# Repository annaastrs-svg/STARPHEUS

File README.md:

STARPHEUS BOT
----

https://annaastrs-svg.github.io/STARPHEUS-PAG/
Take a look to the web page !

[also my build journal :P](JOURNAL.md)

Orpheus Bot It's a robot inspired by the Hack Club mascot (Orpheus).
Starpheus is a Wall-E type robot.
You can control it with a LogiTECH controller (you control its neck with an MG996R servo motor and the TT motors). 
It has 3 OLEDs that make up its eyes and mouth, simulates emotions with basic state machines (scared, happy, sleepy, neutral),
and uses an HC ultrasonic sensor to avoid collisions.
NOTE: this is a rlly full demo jsjjs 

Design
-------
The complete BOT is 31 cm tall, and 31 cm long counting the arms, its designed to look cool (idk if it is,for me it is), i wanted it to be like a Walle-E type.

The design was made so that our little Starpheus isn't heavy and has good mobility.

It has details to be able to put our components and hollow parts so that the chassis isn't heavy and has more mobility, as I already mentioned.

details:

holes for 3 OLED screens (2x 0.96 & 0.91 )
a reset button at the back
the ESP32-S3 connector at the back
the ultrasonic sensor in the front
and spots to attach the motors.

I'm an amateur, this is my biggest solo project so far, and I like to challenge myself.
Honestly, I struggled a lot with this project. I changed everything from one moment to the next thousands of times. It was going to have computer vision and an infrared sensor so you could pet it, it was going to be semi-autonomous, but it was very ambitious. This is the beginning of Starpheus; in the future, I’ll improve it and all these ideas will be more than just ideas. 

PCB
---

CAD
---

I made this EXCEL with all the connections :B

Videos
---
sorry about the quality and my room mess...

https://github.com/user-attachments/assets/39a8d48d-7ff0-484d-94e4-6cae62331124

https://github.com/user-attachments/assets/a8ff2db2-2984-4ae0-9904-147b8f435752

BOM 
--
| Component         | Description                                | Unit | Cost    | Distibutor    | Link                                                                                                                                                                        |
|-------------------|--------------------------------------------|------|---------|---------------|-----------------------------------------------------------------------------------------------------------------------------------------------------------------------------|
| ESP32-S3          | Micro Controler, send code to components   | 1    | $34.91  | AlliExpress        | https://es.aliexpress.com/item/1005009212121307.html?src=bing&exp_tag=pcgcp&albch=shopping&acnt=135095331&albcp=555291703&albag=1299623925852708&slnk=&trgt=pla-2333026235563924&plac=&crea=81226553419370&netw=o&device=c&mtctp=e&utm_source=Bing&utm_medium=shopping&utm_campaign=PA_Bing_MX_Pmax_3C_MAXvalue_20250206_newstore&utm_content=3C&utm_term=ESP32-S3&msclkid=053bb998d0691e21b9cbd3a79d374743&aff_fcid=c5ba799bdfd04e76ae5a24437fb695cd-1782533500453-03069-UneMJZVf&aff_fsk=UneMJZVf&aff_platform=aaf&sk=UneMJZVf&aff_trace_key=c5ba799bdfd04e76ae5a24437fb695cd-1782533500453-03069-UneMJZVf&terminal_id=5927158648684954809663ec4040b6d2&afSmartRedirect=n&gatewayAdapt=glo2esp  |
| DRV8833           | H bridge for motors and control PWM        | 1    | $2.50 | AlliExpress   | https://es.aliexpress.com/item/1005006151344347.html?src=bing&exp_tag=pcgcp&albch=shopping&acnt=135095331&albcp=555291703&albag=1299623925852708&slnk=&trgt=pla-2333026235563924&plac=&crea=81226553419370&netw=o&device=c&mtctp=e&utm_source=Bing&utm_medium=shopping&utm_campaign=PA_Bing_MX_Pmax_3C_MAXvalue_20250206_newstore&utm_content=3C&utm_term=drv8833+bateria+pinout&msclkid=bc6fd8323a4012783781b20d77d54aed&aff_fcid=9159e0ecdd304c6abaf17352f823a6c3-1782533528389-07870-UneMJZVf&aff_fsk=UneMJZVf&aff_platform=aaf&sk=UneMJZVf&aff_trace_key=9159e0ecdd304c6abaf17352f823a6c3-1782533528389-07870-UneMJZVf&terminal_id=5927158648684954809663ec4040b6d2&afSmartRedirect=n&gatewayAdapt=glo2esp |
| OLED.96           | Display, shows data (orpheus eyes)         | 2    | $4.49   | Mercado Libre | https://articulo.mercadolibre.com.mx/MLM-705156753-display-pantalla-oled-128x64-096-para-arduino-_JM?searchVariation=63044404311                                            |
| OLED.91           | Display, shows data (orpheus mouth)        | 1    | $1.31   |   MercadoLibre   |https://www.mercadolibre.com.mx/pantalla-oled-azul-128x32-i2c-091/p/MLM2068167145?pdp_filters=item_id%3AMLM1478945642&from=gshop&matt_tool=15920969&matt_word=&matt_source=microsoft&matt_campaign_id=571305430&matt_ad_group_id=1177579225794197&matt_match_type=e&matt_network=o&matt_device=c&matt_creative=&matt_keyword=&matt_ad_position=&matt_ad_type=&matt_merchant_id=50038545&matt_product_id=MLM2068167145-product&matt_product_partition_id=4577198197450241&matt_target_id=pla-4577198197450241&msclkid=9ee6e6b3969d135712098c8cd8b2aa43&utm_source=bing&utm_medium=cpc&utm_campaign=MLM_ML_BING_AO_CE-ALL-ALL_X_PLA_ALLB_TXS_ALL&utm_term=4577198197450241&utm_content=CE  |
| HC-SR04           | Ultra sonic sensor, meausres distance      | 1    | $2.96   | Mercado Libre |https://www.mercadolibre.com.mx/sensor-de-distancia-hc-sr04-ultrasonico/p/MLM2039690988?pdp_filters=item_id%3AMLM571261161&from=gshop&matt_tool=15920969&matt_word=&matt_source=microsoft&matt_campaign_id=571305430&matt_ad_group_id=1177579225794197&matt_match_type=e&matt_network=o&matt_device=c&matt_creative=&matt_keyword=&matt_ad_position=&matt_ad_type=&matt_merchant_id=50038545&matt_product_id=MLM2039690988-product&matt_product_partition_id=4577198197450205&matt_target_id=pla-4577198197450205&msclkid=7707b5d9707f1734f956dfe63e3cd614&utm_source=bing&utm_medium=cpc&utm_campaign=MLM_ML_BING_AO_CE-ALL-ALL_X_PLA_ALLB_TXS_ALL&utm_term=4577198197450205&utm_content=CE              |
| MG-996R           | Servo Motor, orpheus neck                  | 1    | $7.33   | Amazon | https://www.amazon.com.mx/MG996R-55G-servomotor-Helic%C3%B3ptero-Arduino/dp/B0D7M2Y2BR/ref=asc_df_B0D7M2Y2BR?tag=mxbngshpdsk-20&linkCode=df0&hvadid=82395061852819&hvnetw=o&hvqmt=e&hvbmt=be&hvdev=c&hvlocint=&hvlocphy=151131&hvtargid=pla-4585994287787208&psc=1&msclkid=e6a7df47010d115d6c8eb5784f56fd7d                |
| tt engines        | Movement or orpheus bot                    | 2    | $4.00   | AlliExpress   | https://es.aliexpress.com/item/1005010779121177.html?src=bing&exp_tag=pcgcp&albch=shopping&acnt=135095331&albcp=555291703&albag=1299623925852708&slnk=&trgt=pla2333026235563924&plac=&crea=81226553419370&netw=o&device=c&mtctp=e&utm_source=Bing&utm_medium=shopping&utm_campaign=PA_Bing_MX_Pmax_3C_MAXvalue_20250206_newstore&utm_content=3C&utm_term=motores+tt&msclkid=4604d372fbfe14c3e344b94db561072e&aff_fcid=906d11c52e1f4a55975907ebcbe682d9-1782533793058-08454-UneMJZVf&aff_fsk=UneMJZVf&aff_platform=aaf&sk=UneMJZVf&aff_trace_key=906d11c52e1f4a55975907ebcbe682d9178253379305808454UneMJZVf&terminal_id=5927158648684954809663ec4040b6d2&afSmartRedirect=n&gatewayAdapt=glo2esp                      |
| buck converters   | For Voltage Protecction of the components  | 3    | $6.76   | Amazon   |  https://www.amazon.com.mx/Converter-Aumento-Ajustable-Reguladora-Conector/dp/B09Q8YTQXB/ref=sr_1_8?adgrpid=1165484206288746&dib=eyJ2IjoiMSJ9.TruDAKrU15d416ylBh8ulJJTz2d1TfT8EN7e9dJkodyHHH1od58L1fPMujRYPdf-iyD65iDMp7quqMR4rHF_oqQ558FzdXad7U6iBqxnKLUVJht0rHOsNf8Z6rRik0cXkLeRpQ79jHSn8AZXH9v3RqYukknHhFHUJGS6Di-PsSoyVzjTEjihnYqx9SSuxegqpyq5nz4iXMXztNyK1VH4imimKkbHgfz2UMPh53j9DiQde3CUSugjy8Pt4Wz_rNj58OK0CVWZDV5O15XB4WieNaAyq5raAqeb0MVdrpo1Y.y5zIeOKKhuF_8CNMwzP23gZmRT9i20QQBFSd3UYRtRU&dib_tag=se&hvadid=72843055995125&hvbmt=be&hvdev=c&hvlocphy=151131&hvnetw=o&hvqmt=e&hvtargid=kwd72843484889146%3Aloc119&hydadcr=14088_13417505&keywords=buck+converter&mcid=dc583b2887ca38368f6f683dde6ef2f0&msclkid=d19ed79b5dba1030403cbda4130e4359&qid=1782533818&sr=8-8&ufe=app_do%3Aamzn1.fos.de93fa6a-174c-4df7-be7c-5bc8e9c5a71b                        |
| Resistors 1k      | Kit of resistores, It helps with voltages  | 3    | $1.67   | Amazon   |https://www.amazon.com.mx/Resistencias-Metal-Film-Resistencia-Electr%C3%B3nicos/dp/B0CT529YD5/ref=sr_1_1_sspa?adgrpid=1166582601138475&dib=eyJ2IjoiMSJ9.NBcDPJqTYOjth7gdSySQirqF57sxDL8VWFTI05vC9nj6McOg-YSBZe8EXRi0eC_2E7MKzibLxM7QeVHcHB-Ko1-ebCdCLmKiHIZk1JfymyTa8jkAW23FNCHLAMJkkHtmW02T_EOZNTaL9eMtZ01eDVyzcTlr31lhvyVbtM1L0ijvk4gIRgnyGEiU9Rh7HpPkpj4SuspiLWUM5Q-W2VtRxNUT5J1G7SqDUZ1eaECu0euRlOkuUC3OyOBl_NhPJ95YzFsbwiseZHjBIxn4nGSkh16EDyRwq-q83riR1-KiOHo.1nvw0EbnL_xicWZ96wra5RXpQehdrYCikaisVadVuLE&dib_tag=se&hvadid=72911645984567&hvbmt=be&hvdev=c&hvlocphy=151131&hvnetw=o&hvqmt=e&hvtargid=kwd-72911986116600%3Aloc-119&hydadcr=11033_13513854&keywords=resistor+1k+ohm&mcid=bc221745620433ce85d0638f9c2af89e&msclkid=87cf17f18a9a186803f37dcec453b658&qid=1782533835&sr=8-1-spons&ufe=app_do%3Aamzn1.fos.de93fa6a-174c-4df7-be7c-5bc8e9c5a71b&sp_csd=d2lkZ2V0TmFtZT1zcF9hdGY&psc=1                |
| Capacitores 470uf | Kit of Capacitores, It helps with voltages | 3    | $1.21   | AlliExpress   | https://es.aliexpress.com/item/1005006079381755.html?src=bing&exp_tag=pcgcp&aff_fcid=30b0bfb162a64103b8094d08710fba9a-1782533862684-02992-UneMJZVf&aff_fsk=UneMJZVf&aff_platform=aaf&sk=UneMJZVf&aff_trace_key=30b0bfb162a64103b8094d08710fba9a-1782533862684-02992-UneMJZVf&terminal_id=5927158648684954809663ec4040b6d2&afSmartRedirect=n&gatewayAdapt=glo2esp             |
| Potobard          | Helps With the wiring                      | 1    | $3.41   | Amazon   | https://www.amazon.com.mx/Protoboard-MB-102-Prototipo-soldadura-unidades/dp/B08BCLRLTQ/ref=asc_df_B08BCLRLTQ?tag=mxbngshpdsk-20&linkCode=df0&hvadid=82944817571862&hvnetw=o&hvqmt=e&hvbmt=be&hvdev=c&hvlocint=&hvlocphy=151131&hvtargid=pla-4586544042717891&psc=1&msclkid=0dd1b50556fd178a90addf3a180881ad             |
| Wires Dupont      | Kit, Conects the components                | 1    | $1.79   | Amazon   | https://www.amazon.com.mx/Cables-Pruebas-Opcionales-Surtido-Multicolor/dp/B0DKD315BQ/ref=asc_df_B0DKD315BQ?tag=mxbngshpdsk-20&linkCode=df0&hvadid=82738659152219&hvnetw=o&hvqmt=e&hvbmt=be&hvdev=c&hvlocint=&hvlocphy=151131&hvtargid=pla-4586337884680739&psc=1&msclkid=e88ac20d4e861fde514ea832018665df         |
| Push Botton       | I added for a RST button of ESP32 ()       | 1    | $3.35   | Ebay |     https://www.ebay.com/itm/376667835321?chn=ps&_trkparms=ispr%3D1&amdata=enc%3A1-WCPs7ILQcmM3srRcIAPjQ30&norover=1&mkevt=1&mkrid=711-170539-829218-7&mkcid=2&itemid=376667835321&targetid=4580290580883290&device=c&mktype=&googleloc=151131&poi=&campaignid=605836810&mkgroupid=1227056202074386&rlsatarget=pla-4580290580883290&abcId=&merchantid=51291&msclkid=44e01bfe6e771c83f5b171c1217a5493                                |

There are a lot of components, it's a bit tedious but worth it. I will implement an ESP32 Cam in the future and they cost 3 bucks because I have a spare one. I recommend buying lots of batteries!!

ASSEMBLY 
---

| Orpheus Connections |                 |              |              |           |   |           |                 |                 |             |              |                 |
|---------------------|-----------------|--------------|--------------|-----------|---|-----------|-----------------|-----------------|-------------|--------------|-----------------|
| Come From           |                 | Goes To      |              |           |   | Come From |                 | Goes To         |             | Goes To      |                 |
| Component           |             Pin | Component    | Pin          |           |   | Component |             Pin | Component       | Pin         | Component    |             Pin |
| ESP32 S3            | 9               | OLED 1       | SCK          |           |   | Buck 2    | out +           | Capacitor 470uf | Positive +  | MG996R       | 5V              |
| ESP32 S3            | 8               | OLED 1       | SDA          |           |   |           |                 | Capacitor 470uf | Negative -  | Protoboard 1 | Negative        |
| ESP32 S3            | 14              | MG996R       | S            |           |   | Buck 2    | out -           | Protoboard1     | Negative -  |              |                 |
| ESP32 S3            | 10              | OLED 2       | SDA          |           |   | Buck 2    | in +            | Protoboard 2    | Positive +  |              |                 |
| ESP32 S3            | 11              | OLED 2       | SCK          |           |   | Buck 2    | in -            | Protoboard1     | Negative -  |              |                 |
| ESP32 S3            | 38              | OLED 3       | SDA          |           |   |           |                 |                 |             |              |                 |
| ESP32 S3            | 39              | OLED 3       | SCK          |           |   | Buck 1    | out +           | Capacitor 470uf | Positive +  | DRV8833      | 5V              |
| ESP32 S3            | 15              | DRV8833      | IN1          | A         |   |           |                 | Capacitor 470uf | Negative -  | Protoboard 1 | Negative        |
| ESP32 S3            | 16              | DRV8833      | IN2          | A         |   | Buck 1    | out -           | Protoboard 1    | Negative    |              |                 |
| ESP32 S3            | 17              | DRV8833      | IN3          | B         |   | Buck 1    | in +            | Protoboard 2    | Positive +  |              |                 |
| ESP32 S3            | 18              | DRV8833      | IN4          | B         |   | Buck 1    | in-             | Protoboard 1    | Negative -  |              |                 |
| ESP32 S3            | 5               | HC-SR04      | TRIG         |           |   |           |                 |                 |             |              |                 |
| ESP32 S3            | 6               | R1 (1kohm)    | ECHO         | R2 (2kohm) |   | BATTERY   | OUT +           | Protoboard 2    | Positive +  |              |                 |
| MG996R              | GND             | Protoboard 1 | Negative -   |           |   | BATTERY   | OUT -           | Protoboard 1    | Negative -  |              |                 |
| OLED 0.96  (1 & 2)  | GND             | Protoboard 1 | Negative -   |           |   |           |                 |                 |             |              |                 |
| OLED 0.96  (1 & 2)  | 5V              | Protoboard 1 | Positive +   |           |   |           |                 |                 |             |              |                 |
| OLED 0.91           | GND             | Protoboard 1 | Negative -   |           |   |           |                 |                 |             |              |                 |
| OLED 0.91           | 5V              | Protoboard 1 | Positive +   |           |   |           |                 |                 |             |              |                 |
| HC-SR04             | GND             | Protoboard 1 | Negative -   |           |   |           |                 |                 |             |              |                 |
| DRV8833             | GND             | Protoboard 1 | Negative -   |           |   |           |                 |                 |             |              |                 |
| DRV8833             | OUT1            | MOTOR A      | NO POLARIDAD |           |   |           |                 |                 |             |              |                 |
| DRV8833             | OUT2            | MOTOR A      | NO POLARIDAD |           |   |           |                 |                 |             |              |                 |
| DRV8833             | OUT3            | MOTOR B      | NO POLARIDAD |           |   |           |                 |                 |             |              |                 |
| DRV8833             | OUT4            | MOTOR B      | NO POLARIDAD |           |   |           |                 |                 |             |              |                 |
|                     |                 |              |              |           |   |           |                 |                 |             |              |                 |
|                     |                 |              |              |           |   |           |                 |                 |             |              |                 |
|                     |                 |              |              |           |   |           |                 |                 |             |              |                 |
|                     |                 |              |              |           |   |           |                 |                 |             |              |                 |
|                     |                 |              |              |           |   |           |                 |                 |             |              |                 |
|                     |                 |              |              |           |   |           |                 |                 |             |              |                 |
|                     |                 |              |              |           |   |           |                 |                 |             |              |                 |

Wiring Little Tutorial, Moustly Explication
----

To build this, there are several things you need to take into account. 
First, the common GND that I implemented with my trusted protoboard: absolutely all the GNDs go to the negative of the protoboard. In the wiring table I made, it's the negative of protoboard 1.
I have divided my protoboard into two sections: the common GND and the 5V for the ESP, the OLEDs, and the ultrasonic sensor,
The second part is for connecting the battery directly and the IN+ of the buck converters, Why don't they go with the other components and get excluded? That's because if we put them together, we’ll damage the components, and that wouldn’t be good. Make sure everything is connected well because sometimes things get loose on the protoboard.  

It’s very logical; you need to make sure the circuit closes properly so it works, and what killed me the most in this project were the voltages, The recommended battery is 7.4V, but after 2 hours of testing it runs out. You can use 6 AA batteries in series or do what I did,I made a long cable by stripping one I had and adapted it to connect to Starpheus. It's like it has a strap, but it's really useful and functional if you're poor like me and can't be buying batteries every 3 hours.

Use 2 capacitors and 3 resistors, 1 capacitor of 470uF for the out+ of the two buck converters (motor and servomotor) so they don't cause power spikes. The resistors are for the ultrasonic sensor. I put a 1k resistor on the wire going from pin 5 of the ESP32S3 to the breadboard; one leg touches that wire directly and the other goes to another wire that goes to the echo of the HCSR04. On that same pin, I directly put two 1k resistors in series to make 2k, and the other leg goes to GND. This is so that the HCSR04 doesn't make too much noise since it's at 5V along with the OLEDs and the ESP32S3.  

Since we have many components drawing a lot of current, we have to consider the motors. In the math part, you need to know a bit about static friction and kinetic friction. Kinetic friction has to be greater than static friction because generally the coefficient of static friction is always higher than the kinetic one, so the motor force has to be greater than the maximum static friction force.

LICENSE
---
MIT

PS:(sorry for some gramatic errors and bad spelling, enlish is not my best lenguage)
thank you a lot hack club staff and people looking at this <3

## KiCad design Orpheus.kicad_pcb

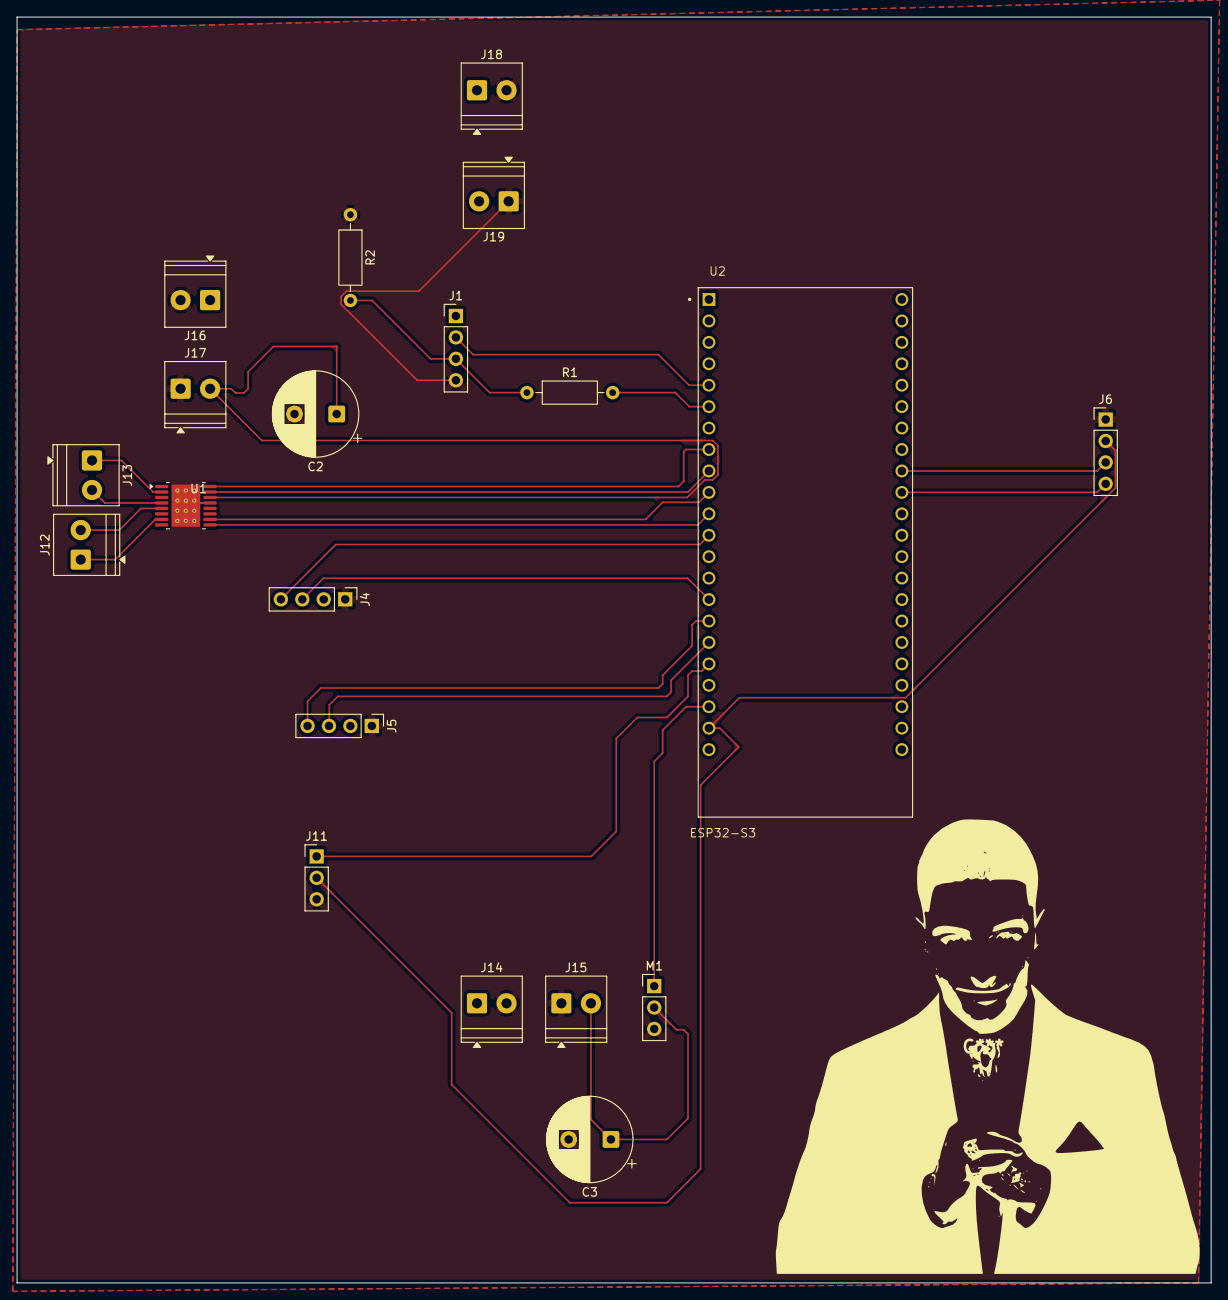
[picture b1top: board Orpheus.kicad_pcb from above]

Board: 2 copper layers, 141.5 x 150.0 mm, 20 parts (0 on the bottom side), 21 nets.

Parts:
C2, C3: 470uf; CP_Radial_D10.0mm_P5.00mm
J1: HC-SR04; PinHeader_1x04_P2.54mm_Vertical
J4: OLED 0.91; PinHeader_1x04_P2.54mm_Vertical
J5, J6: OLED 0.96 (2); PinHeader_1x04_P2.54mm_Vertical
J11: IR; PinHeader_1x03_P2.54mm_Vertical
J12: Motor B; TerminalBlock_Phoenix_PT-1,5-2-3.5-H_1x02_P3.50mm_Horizontal
J13: Motor A; TerminalBlock_Phoenix_PT-1,5-2-3.5-H_1x02_P3.50mm_Horizontal
J14, J18: BUCK 2 IN; TerminalBlock_Phoenix_PT-1,5-2-3.5-H_1x02_P3.50mm_Horizontal
J15, J19: BUCK 2 OUT; TerminalBlock_Phoenix_PT-1,5-2-3.5-H_1x02_P3.50mm_Horizontal
J16: BUCK 1 IN; TerminalBlock_Phoenix_PT-1,5-2-3.5-H_1x02_P3.50mm_Horizontal
J17: BUCK 1 OUT; TerminalBlock_Phoenix_PT-1,5-2-3.5-H_1x02_P3.50mm_Horizontal
M1: MG996R; PinHeader_1x03_P2.54mm_Vertical
R1: 2k; R_Axial_DIN0207_L6.3mm_D2.5mm_P10.16mm_Horizontal
R2: 1k; R_Axial_DIN0207_L6.3mm_D2.5mm_P10.16mm_Horizontal
U1: DRV8833PWP; HTSSOP-16-1EP_4.4x5mm_P0.65mm_EP3.4x5mm_Mask2.46x2.31mm_The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
U2: ESP32-S3; XCVR_ESP32-S3-DEVKITC-1U-N8R2

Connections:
+: C2.1, C3.1, J1.1, J4.2, J5.2, J6.2, J11.2, J14.1, J15.2, J16.1, J17.2, J18.1, J19.2, M1.2 (+), U1.14 (VINT), U2.J1_21 (5V0)
-: C2.2, C3.2, J1.4, J4.1, J5.1, J6.1, J11.3, J14.2, J15.1, J16.2, J17.1, J18.2, J19.1, M1.3 (-), R2.1, U1.13 (GND), U1.17 (GND)
ECHO: J1.3, R1.1, R2.2
unnamed: J12.1, U1.7 (BOUT1)
unnamed: J12.2, U1.5 (BOUT2)
unnamed: J13.1, U1.2 (AOUT1)
unnamed: J13.2, U1.4 (AOUT2)
unnamed: M1.1 (PWM), U2.J1_20 (GPIO14)
unnamed: U1.16 (AIN1), U2.J1_8 (GPIO15)
unnamed: U1.15 (AIN2), U2.J1_9 (GPIO16)
unnamed: U1.9 (BIN1), U2.J1_11 (GPIO18)
unnamed: U1.10 (BIN2), U2.J1_10 (GPIO17)
unnamed: R1.2, U2.J1_6 (GPIO6)
S: J11.1, U2.J1_18 (GPIO12)
SCK B: J4.3, U2.J1_15 (GPIO9)
SCK OD: J5.3, U2.J1_17 (GPIO11)
SCK OI: J6.3, U2.J3_9 (MTCK/GPIO39)
SDA B: J4.4, U2.J1_12 (GPIO8)
SDA OD: J5.4, U2.J1_16 (GPIO10)
SDA OI: J6.4, U2.J3_10 (GPIO38)
TRIG: J1.2, U2.J1_5 (GPIO5)

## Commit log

2026-06-25 CAD . gerber files
2026-06-25 CAD PCB
2026-06-27 Revise README with updated wiring and assembly details
    Updated the wiring table and BOM with new components and links. Added assembly instructions and wiring tutorial for the project.
2026-06-28 Softwere.ino
2026-06-28 Fix formatting in README.md
    Corrected formatting and punctuation in README.

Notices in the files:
README.md:
LICENSE:
MIT
PS:(sorry for some gramatic errors and bad spelling, enlish is not my best lenguage)
thank you a lot hack club staff and people looking at this <3
